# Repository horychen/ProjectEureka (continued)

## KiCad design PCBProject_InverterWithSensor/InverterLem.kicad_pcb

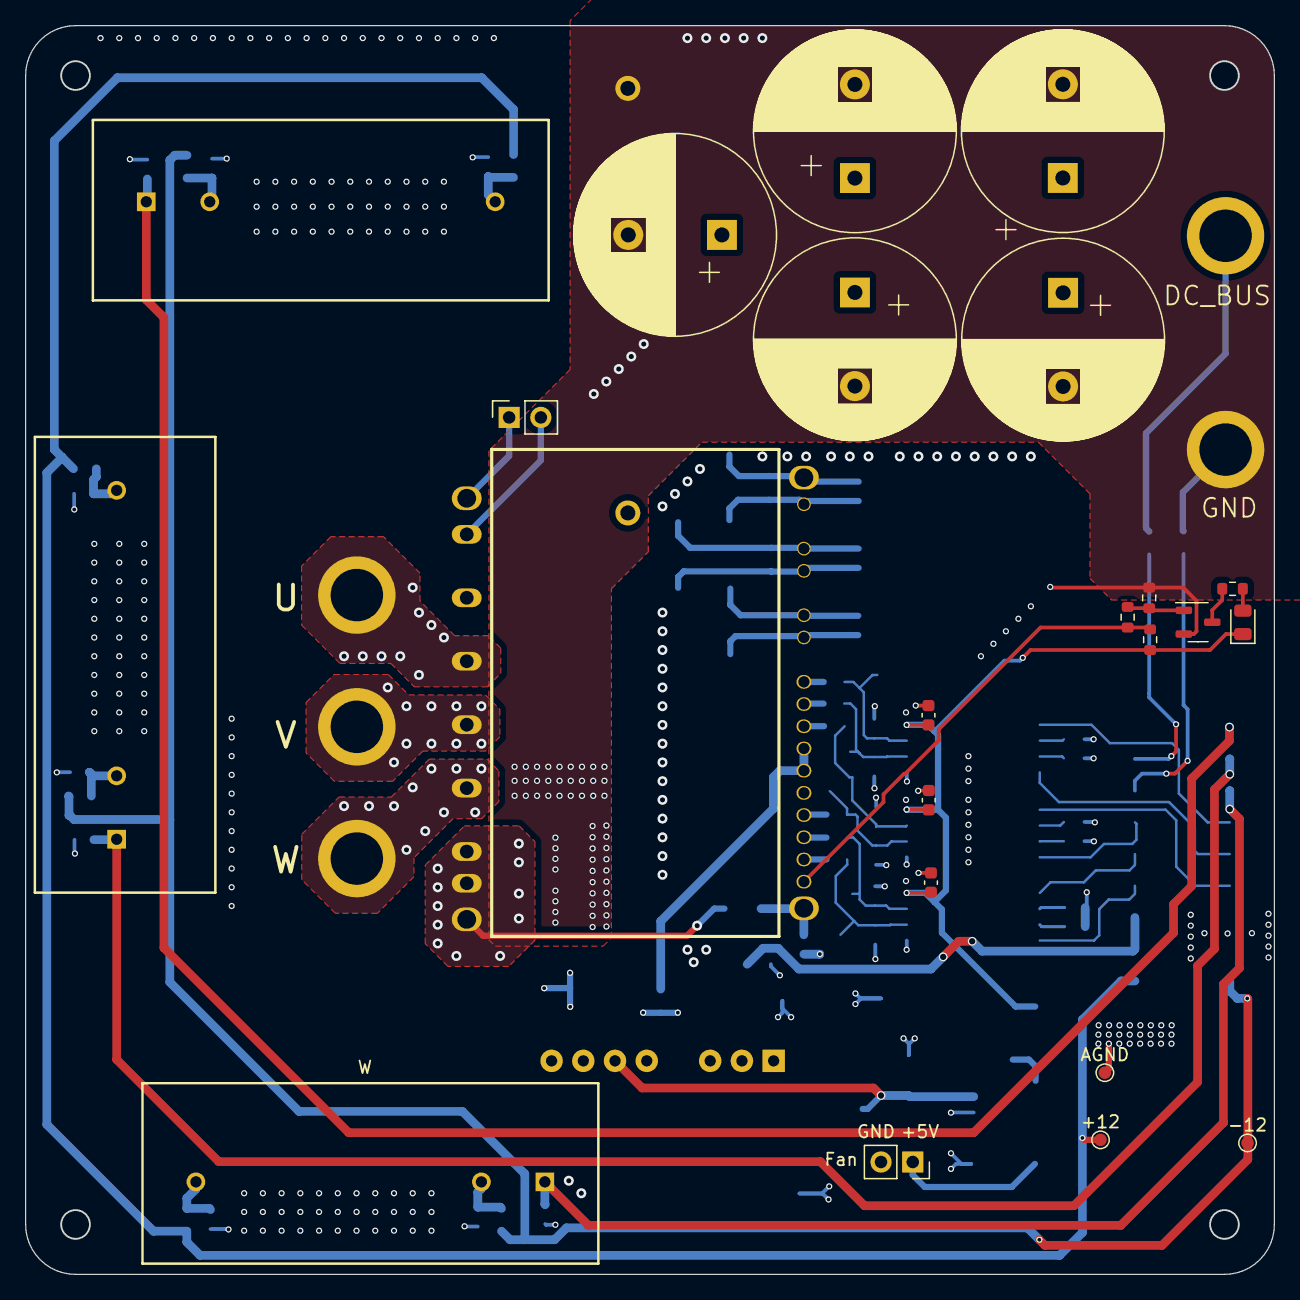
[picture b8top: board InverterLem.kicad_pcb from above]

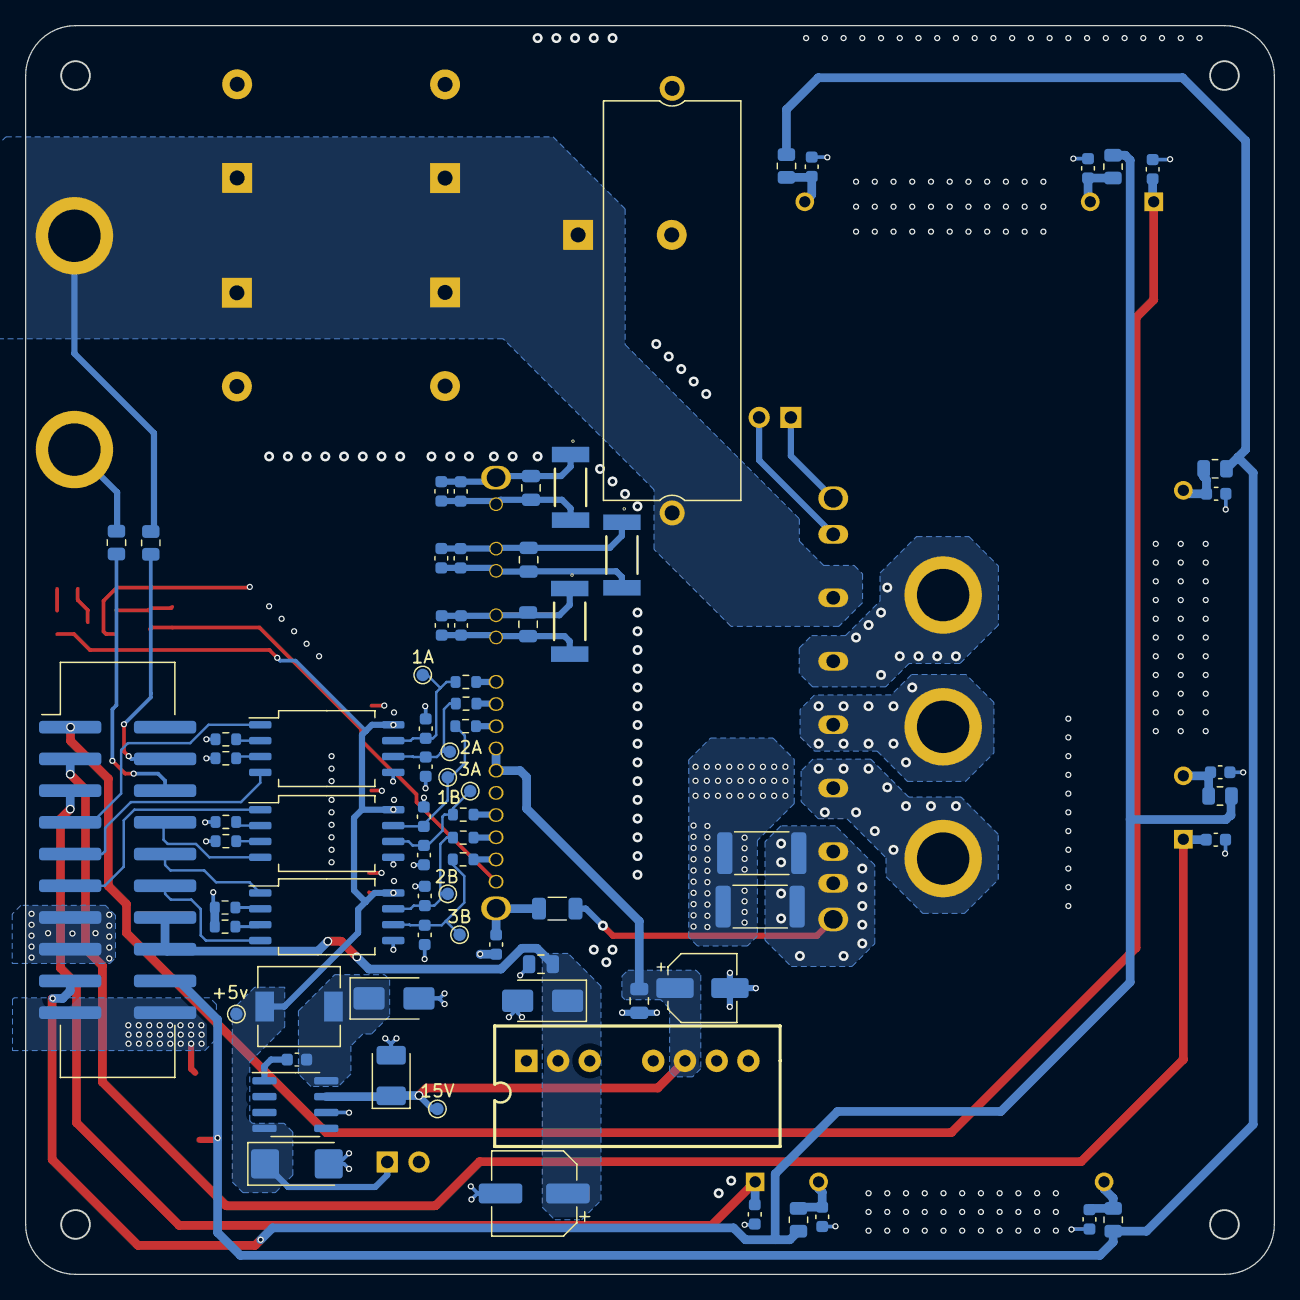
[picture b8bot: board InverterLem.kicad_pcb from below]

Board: 4 copper layers, 100.0 x 100.0 mm, 103 parts (76 on the bottom side), 63 nets.

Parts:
1A: OPWM1A; TestPoint_Pad_D1.0mm
1B: OPWM1B; TestPoint_Pad_D1.0mm
2A: OPWM2A; TestPoint_Pad_D1.0mm
2B: OPWM2B; TestPoint_Pad_D1.0mm
3A: OPWM3A; TestPoint_Pad_D1.0mm
3B: OPWM3B; TestPoint_Pad_D1.0mm
15V: Test15V; TestPoint_Pad_D1.0mm
+5v: Test5V; TestPoint_Pad_D1.0mm
+12: +12; TestPoint_Pad_D1.0mm
-12: -12; TestPoint_Pad_D1.0mm
A1, A2, A3: LA55-P; XDCR_LA55-P
A6: VRB1215S-6WR3; VRB_S-6WR3
AGND: AGND; TestPoint_Pad_D1.0mm
C1, C2, C3, C7, C8, C9: 47nf; C_0603_1608Metric
C4, C5, C6: 4.7uF; C_0603_1608Metric
C19, C59, C60, C61, C62: 47uF/450V; CP_Radial_D16.0mm_P7.50mm
C20: 15uF 50V Tantalum; CP_EIA-3528-21_Kemet-B_Pad1.50x2.35mm_HandSolder
C23: 10nF; C_0603_1608Metric
C24: 1nf; C_0603_1608Metric
C25: 68uF 16V Tantalum; CP_EIA-6032-28_Kemet-C_Pad2.25x2.35mm_HandSolder
C27, C38, C39: 100nf; C_0603_1608Metric
C40, C41, C42, C45, C46, C47: 2.2uf; C_0603_1608Metric
C43, C44, C49, C54, C55, C57: 100pf; C_0603_1608Metric
C48, C56: 100nF; C_0805_2012Metric
C50, C51, C52: 100nf; C_0805_2012Metric
C53: 100uf 50V; CP_Elec_6.3x7.7
C58: 22uf 25V; CP_Elec_5x5.4
D1, D2: 1N5819; D_SMA
D3: LEDRED; LED_0805_2012Metric
IC1, IC2, IC3: TLP2270_D4-LF4,E; SOIC-8_7.5x5.85mm_P1.27mm
J1: Phase 1; M3_smt
J2: DSP; IDC-Header_2x10_P2.54mm_Vertical_SMD
J3: Phase 2; M3_smt
J4: Phase 3; M3_smt
J5: Fan; PinSocket_1x02_P2.54mm_Vertical
J6: DC_BUS; M3_smt
J7: GND; M3_smt
J9: Conn_01x02_Pin; PinSocket_1x02_P2.54mm_Vertical
L1: 47uH; L_6.3x6.3_H3
Q1: FNC42060F
Q2: FMMT618TA; SOT-23-3
R11, R12: 2M; R_0805_2012Metric
R13, R14, R16, R21, R22, R23: 750R; R_0603_1608Metric
R24, R25: 8mR; R_2512_6332Metric
R26: 2k; R_1206_3216Metric
R27, R28, R29, R30, R31, R32: 100R; R_0603_1608Metric
R33, R34: 10K; R_0603_1608Metric
R35: 2K; R_0603_1608Metric
R36: 301R; R_0603_1608Metric
RB1, RB2, RB3, RB4, RB5, RB6: 0R; R_0805_2012Metric
U2: LM2675M-5.0; SOIC-8_3.9x4.9mm_P1.27mm
Z1, Z2, Z3: ZM4746A-GS08; MELF_DO-213AB

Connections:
12VGND: A6.1 (GND), C1.2, C2.2, C3.2, C4.2, C5.1, C6.1, C7.2, C8.2, C9.2, C48.1, C53.2, D2.2 (A), J2.13, J2.15
+5V1: +5v.1, C25.1, C27.2, C38.2, C39.2, D3.1 (A), IC1.8 (VDD), IC2.8 (VDD), IC3.8 (VDD), J5.1, L1.2, R33.1, U2.4 (FB)
+12: +12.1, J2.18, RB1.2, RB2.2, RB3.1
+15V1: 15V.1, A6.6 (+Vo), C20.1, C56.2, C58.1, Q1.16 (VCC(L)), Q1.17 (VCC(H)), U2.7 (VIN)
-12: -12.1, J2.17, RB4.2, RB5.2, RB6.2
/CSC: Q1.7 (NU), Q1.8 (NV), Q1.9 (NW), R24.1, R25.1, R26.2
/CSO1: A2.1 (M), C6.2, J2.1
/CSO2: A3.1 (M), C5.2, J2.3
/CSO3: A1.1 (M), C4.1, J2.5
/DC_BUS_2M: J2.4, R11.2
/DSP_PWM1_~FAULT_5V: Q1.11 (VFO), R33.2, R34.2
/GND_2M: J2.6, R12.2
/M+1: C40.1, C45.1, C50.1, Q1.26 (VB(U)), Z1.1 (K)
/M+2: C41.1, C46.1, C51.1, Q1.24 (VB(V)), Z2.1 (K)
/M+3: C42.1, C47.1, C52.1, Q1.22 (VB(W)), Z3.1 (K)
/M-1: C40.2, C45.2, C50.2, Q1.25 (VS(U)), Z1.2 (A)
/M-2: C41.2, C46.2, C51.2, Q1.23 (VS(V)), Z2.2 (A)
/M-3: C42.2, C47.2, C52.2, Q1.21 (VS(W)), Z3.2 (A)
/OPWM1A: 1A.1, C54.2, IC1.7 (VO1(OUTPUT_1)), R30.2
/OPWM1B: 1B.1, C43.2, IC2.6 (VO2_(OUTPUT2)), R27.2
/OPWM2A: 2A.1, C55.2, IC1.6 (VO2_(OUTPUT2)), R31.2
/OPWM2B: 2B.1, C44.2, IC3.7 (VO1(OUTPUT_1)), R28.2
/OPWM3A: 3A.1, C57.2, IC2.7 (VO1(OUTPUT_1)), R32.2
/OPWM3B: 3B.1, C49.2, IC3.6 (VO2_(OUTPUT2)), R29.2
/PWM1A_5V: IC1.1 (ANODE_1), J2.7
/PWM1B_5V: IC2.4 (ANODE_2), J2.8
/PWM2A_5V: IC1.4 (ANODE_2), J2.9
/PWM2B_5V: IC3.1 (ANODE_1), J2.10
/PWM3A_5V: IC2.1 (ANODE_1), J2.11
/PWM3B_5V: IC3.4 (ANODE_2), J2.12
/U: J1.1, Q1.4 (U)
/V: J3.1, Q1.5 (V)
/W: J4.1, Q1.6 (W)
AGND: AGND.1, J2.19, J2.20, R13.2, R14.2, R16.2, R21.2, R22.2, R23.2
D12V1: A6.2 (Vin), C48.2, C53.1, D2.1 (K), J2.14, J2.16
DC_BUS: C19.1, C59.1, C60.1, C61.1, C62.1, J6.1, Q1.3, R11.1
GND: A6.7 (0V), C19.2, C20.2, C24.1, C25.2, C27.1, C38.1, C39.1, C43.1, C44.1, C49.1, C54.1, C55.1, C56.1, C57.1, C58.2, C59.2, C60.2, C61.2, C62.2, D1.2 (A), IC1.5 (GND), IC2.5 (GND), IC3.5 (GND), J5.2, J7.1, Q1.15 (COM), Q2.2 (E), R12.1, R24.2, R25.2, R35.2, U2.6 (GND)
unnamed: A1.2 (NEG), C8.1, RB4.1
unnamed: A1.3 (POS), C1.1, RB1.1
unnamed: A2.2 (NEG), C9.1, RB5.1
unnamed: A2.3 (POS), C2.1, RB2.1
unnamed: A3.2 (NEG), C3.1, RB6.1
unnamed: A3.3 (POS), C7.1, RB3.2
unnamed: C23.2, D1.1 (K), L1.1, U2.8 (VOUT)
unnamed: D3.2 (K), R36.2
unnamed: IC1.2 (CATHODE_1), R13.1
unnamed: IC1.3 (CATHODE_2), R14.1
unnamed: IC2.2 (CATHODE_1), R16.1
unnamed: IC2.3 (CATHODE_2), R21.1
unnamed: IC3.2 (CATHODE_1), R22.1
unnamed: IC3.3 (CATHODE_2), R23.1
unnamed: J9.1, Q1.1 (VTH)
unnamed: J9.2, Q1.2 (RTH)
unnamed: C24.2, Q1.10 (CSC), R26.1
unnamed: Q1.20 (IN(UH)), R30.1
unnamed: Q1.14 (IN(UL)), R27.1
unnamed: Q1.19 (IN(VH)), R31.1
unnamed: Q1.13 (IN(VL)), R28.1
unnamed: Q1.18 (IN(WH)), R32.1
unnamed: Q1.12 (IN(WL)), R29.1
unnamed: Q2.1 (B), R34.1, R35.1
unnamed: Q2.3 (C), R36.1
unnamed: C23.1, U2.1 (CB)

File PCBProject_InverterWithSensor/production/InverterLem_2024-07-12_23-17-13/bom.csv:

Designator,Footprint,Quantity,Value,LCSC Part #
+12,TestPoint_Pad_D1.0mm,1,+12,
+5v,TestPoint_Pad_D1.0mm,1,Test5V,
-12,TestPoint_Pad_D1.0mm,1,-12,
15V,TestPoint_Pad_D1.0mm,1,Test15V,
1A,TestPoint_Pad_D1.0mm,1,OPWM1A,
1B,TestPoint_Pad_D1.0mm,1,OPWM1B,
2A,TestPoint_Pad_D1.0mm,1,OPWM2A,
2B,TestPoint_Pad_D1.0mm,1,OPWM2B,
3A,TestPoint_Pad_D1.0mm,1,OPWM3A,
3B,TestPoint_Pad_D1.0mm,1,OPWM3B,
"A1, A2, A3",XDCR_LA55-P,3,LA55-P,
A6,VRB_S-6WR3,1,VRB1215S-6WR3,
AGND,TestPoint_Pad_D1.0mm,1,AGND,
"C1, C2, C3, C7, C8, C9",0603,6,47nf,
"C19, C59, C60, C61, C62",CP_Radial_D16.0mm_P7.50mm,5,47uF/450V,
C20,CP_EIA-3528-21_Kemet-B_Pad1.50x2.35mm_HandSolder,1,15uF 50V Tantalum,
C23,0603,1,10nF,
C24,0603,1,1nf,
C25,CP_EIA-6032-28_Kemet-C_Pad2.25x2.35mm_HandSolder,1,68uF 16V Tantalum,
"C27, C38, C39",0603,3,100nf,
"C4, C5, C6",0603,3,4.7uF,
"C40, C41, C42, C45, C46, C47",0603,6,2.2uf,
"C43, C44, C49, C54, C55, C57",0603,6,100pf,
"C48, C50, C51, C52, C56",0805,5,100nF,
C53,CP_Elec_6.3x7.7,1,100uf 50V,
C58,CP_Elec_5x5.4,1,22uf 25V,
"D1, D2",D_SMA,2,1N5819,
D3,0805,1,LEDRED,
"IC1, IC2, IC3",SOIC-8_7.5x5.85mm_P1.27mm,3,"TLP2270_D4-LF4,E",
J1,M3_smt,1,Phase 1,
J2,IDC-Header_2x10_P2.54mm_Vertical_SMD,1,DSP,
J3,M3_smt,1,Phase 2,
J4,M3_smt,1,Phase 3,
J5,PinSocket_1x02_P2.54mm_Vertical,1,Fan,
J6,M3_smt,1,DC_BUS,
J7,M3_smt,1,GND,
J9,PinSocket_1x02_P2.54mm_Vertical,1,Conn_01x02_Pin,
L1,L_6.3x6.3_H3,1,47uH,
Q1,FNC42060F,1,FNC42060F,
Q2,SOT-23-3,1,FMMT618TA,
"R11, R12",0805,2,2M,
"R13, R14, R16, R21, R22, R23",0603,6,750R,
"R24, R25",2512,2,8mR,
R26,1206,1,2k,
"R27, R28, R29, R30, R31, R32",0603,6,100R,
"R33, R34",0603,2,10K,
R35,0603,1,2K,
R36,0603,1,301R,
"RB1, RB2, RB3, RB4, RB5, RB6",0805,6,0R,
U2,SOIC-8_3.9x4.9mm_P1.27mm,1,LM2675M-5.0,
"Z1, Z2, Z3",MELF_DO-213AB,3,ZM4746A-GS08,

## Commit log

2023-12-11 add spi-can and encoder boards
2023-12-12 change power supp;y to 12 and maintain 15 pulgin
2023-12-12 power schematic finished
2023-12-13 finish inverter PCB in kicad
2023-12-13 update sheet1
2023-12-13 sensorLEM
2023-12-13 add REF_3V
2023-12-13 position changes
2023-12-14 Power PCB finished
2023-12-14 sheet1 add PWM.
2023-12-14 Update sheet3 12VGND.
2023-12-14 YZZ: update the power names.
2023-12-14 ignore Kicad LCK file
2023-12-14 remove +-15V add 12VGND
2023-12-15 sheet1 add power
2023-12-15 Update Power PCB, this is final version
2023-12-15 Update extension
2023-12-16 extensionBoard again
2023-12-16 update inverter board
2023-12-17 update Extension sch, kicad version
2023-12-17 Update Power board, PDN is failed
2023-12-18 add footprint for kicad
2023-12-18 update sheet1 (kicad)
2023-12-18 add footprint again(
2023-12-20 Add sheet pcb.
2023-12-20 Place the components.
2023-12-20 Add ExtensionSimple board for fast prototyping.
2023-12-23 New kicad library and send sheet1 for production.
2023-12-27 fix bugs in power and LEM boards
    12VGND should be negative input to amp on LEM. May be also need single connected?
2024-01-02 sensor12VGND
2024-01-03 Add ExtensionSimple2
2024-01-04 comnponents kayout in the pcb
2024-01-04 Components layout
2024-01-05 block routing done.
2024-01-05 cross check of invterter
2024-01-05 add inverter board production files
2024-01-05 CPU DSP new footprint
2024-01-05 extension board layout
2024-01-05 Add dsp 240 smd footprint
2024-01-05 HY加油
2024-01-05 Revert "HY加油"
    This reverts commit aaa1912d429fb000e99d7c8797d7335188b5b639.
    rollback
2024-01-05 Power layout
2024-01-05 HY finished layout GND铺铜
2024-01-06 extension Update
    need double check
2024-01-06 submit extension board
2024-01-06 add sheet6 encoder kicad files.
2024-01-08 add RS485 board to project
2024-01-15 add sheet6 encoder board provided by wang, qian
2024-01-16 alter encoder, making it better.
2024-01-19 改善编码器
2024-01-29 重新布线+原图备份x1
2024-01-29 01.29pcb更改
2024-02-21 corrret Extension size
2024-02-22 correct Extension-IPM1 size
2024-02-25 renew Encoder--kicad_sheet6
2024-02-26 将编码器改为两层，文件为：kicad_encoder.kicad_pcb
2024-03-02 SensorLEM版本(右翼)布线完毕
2024-03-05 布线电流传感器完毕
    “左翼”电流传感器文件为：SensorLEM(left).kicad_pcb
2024-03-06 Eureka1.0的底板，可以在此基础上改版
2024-03-06 完善电流传感器Pcb(只是加了30pin丝印)
2024-03-12 add some text items
2024-03-17 底板原理图中加入RS485通讯芯片—-SN65HVD75
2024-03-20 解决电流传感器中的错误：电线与边缘太近了！
2024-03-20 生成电流传感器production;生成inverter的bom;生成Encoder的bom与production
2024-03-22 底板中增加了CAN转TTL模块，并初步修改了底板的尺寸
2024-03-22 确定底板尺寸，目前只差布线
2024-03-22 底板布线基本完毕，但是还有些地方出现了混乱，仍需改进
2024-03-23 底板布线完毕！
2024-03-24 Add ExtensionSimple3
2024-03-25 生成底板的bom和production
2024-03-25 更改底板布局，将新加元器件放在了背面
2024-03-25 Update ExtensionSimple3 schematic and pcb
2024-03-30 finish DACBoard and redefine the pins of DACBoard
2024-04-01 finish ExtensionSimple3
2024-04-01 Fix Teardrop
2024-04-03 @Eorl 1. 需要第二套高速SPI，把 SPI-A 引出来用于DSP之间50MHz通讯。 2. 给I2C找到合适的GPIO引脚，更新原理图 3. 随便找一排GPIO引脚拉到2.54mm的排针上，为INPUT-XBAR预留 4. CAN的12V电源应该是数字电源，现在是用电流传感器的12V，not good 5. CAN排针之间太近，485排针之间太近 6. QEP不需要那个2*10的简牛，删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
2024-04-07 finish 7 commits
2024-04-10 add inverter v0.3
2024-04-10 finish happy485
2024-04-12 generate bom_power
2024-04-14 fix some extension bugs
2024-04-19 let VDD to 485
2024-04-25 fix VDD and ref_3V, DC_bus location
2024-05-31 some location has been fixed
2024-06-05 update sensorlem2(right) to adapt to extensionborad3
2024-06-30 Divide DSP, and Matched DC bus Net Lengths
2024-06-30 three DSP's symbols and footprints
2024-07-12 extension board 3.0 for 1 to 4.
2024-07-12 add I2C2 and SPI B
2024-07-13 add 12 LTC6240HV
2024-07-18 add: readme
2024-07-18 revise on readme
2024-07-19 Create LICENSE
2024-07-20 fix SCI_C AND D, ADD ECAP TO 1TO2
2024-07-20 add new inverter with LEM current sensor
2024-07-20 fix SCI_C and D, add ECAP to 1TO4, but 1TO4 haven't finish.
2024-07-26 add a redeme file named 'ReadMe_SensorLEM.md' about SensorLEM
2024-07-26 add a readme file named 'ReadMe_SensorLEM.md' about SensorLEM
2024-07-26 pull the remote library to the local location
2024-08-14 修改UVW顺序
2024-08-17 SensorLEM: Add sensorLEM_portable file(From Altium Designer file 'SensorLEM_Guan' to Kicad).
2024-08-19 sensorLEM_portable的原理图和Pcb都已经制作完毕，bom表和制作文件也都已经生成。
2024-09-07 add ecap to '1to4', fix the GPIO bugs of SCI C and SCI D.
2024-09-07 modified uvw
2024-09-10 add tear drop
2024-10-27 fomula four2one, but the signal of current sensor is not good.
2024-10-31 SensorLEM:更新ReadMe文件
2024-11-06 Inverter：Generating .zip of Inverter for LichuangEDA.
2024-12-16 waiting for improving quality of current sensor signals
2025-01-23 Create PowerBoard kicad version
2025-02-19 修改DAC接口定义
2025-04-08 重定义了DAC接口和修复了底板的PWM的bug，还需实现DAC电源集成
2025-05-25 DAC for 28388
2025-05-25 fix bugs
2025-10-01 修改SPI-B为高速SPIGPIO
2025-10-09 添加ADC拓展板
2025-10-10 布局50%请求援助
2025-10-10 完成ADC拓展
2025-10-13 添加绝对值编码器接口和IPM接口
2025-10-18 377新板子暂停
